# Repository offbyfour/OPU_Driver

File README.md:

# Blu-Ray Lithography
## Introduction
This is the project page for a lithography system based on repurposing Blu-Ray drives. The initial goal is to reach a feature size of at least 500nm (2x the Blu-ray laser spot size). As a stretch goal, we would like to also use the sled and spindle motors as high speed nano-positioners and to spin coat and cure photo-resin.

## Safety
✓ Safety goggles/glasses are absolutely necessary.
A laser dot contains a large amount of energy in such a small space, in the form of light. Your eyes are extremely sensitive to light, and a direct exposure to this very dense energy light for less than a second will blind you for life. We can prevent this by wearing a special type of light filtering glasses, somewhat like the way sunglasses work. But, sunglasses will not work as laser safety glasses. These glasses need to be coated for the correct wavelength. Do not purchase any laser safety glasses under $30, buy from an authorized and reputable seller such as survival lasers. $5 lenses from China will not be sufficient, and have been proven unsafe.

Currently Recommended: https://www.amazon.com/Tool-Klean-Safety-Glasses-Protection/dp/B081BHTJT8/ref=sr_1_5

✓ Be fully aware of what you are pointing at.
With a massive amount of light comes the heat as well. Lasers higher than Class IV (>500mW) burn certain objects very easily, lower powers do burn as well but not as intensely. Lasers like this can most definitely burn furniture such as carpet and couches, hardwood floors, curtains, walls etc. You need to make sure that you are not burning anything against your desire. If the heat build up in an object from a laser is sufficient enough, the object could be set on fire.

✓ Keep in mind of any dangerous objects/surfaces.
Look out for anything noticeably reflective/smooth such as a mirror, polished metal, or even something smooth like a desk. The last thing you want is a laser beam reflected back at you into your eye. Even with safety goggles/glasses, you should not take a chance. Something else dangerous that you need to look out for are flammable items, a high powered laser can easily ignite a match or alcohol. CAREFUL WITH WINDOWS - None are 100% transparent, and WILL reflect a solid beam back towards you, this goes for any type of glass at all. All reflected beams are also a danger and this is no exception. Windows are also a bad thing to be pointing a laser through, you don't know exactly where/what you'll hit.

__________________________________________________

Be careful with lasers, treat them like a loaded gun. It is very easy to create dangerous situations with a laser if you're not careful, be responsible and eliminate that possibility!
Source: laserpointerforums.com
​
## Project Status

Right now, the first project for this technology (Lithography Spinner V1) is in the research/idea stage. See work in progress page for details on upcoming tasks if you want to contribute.

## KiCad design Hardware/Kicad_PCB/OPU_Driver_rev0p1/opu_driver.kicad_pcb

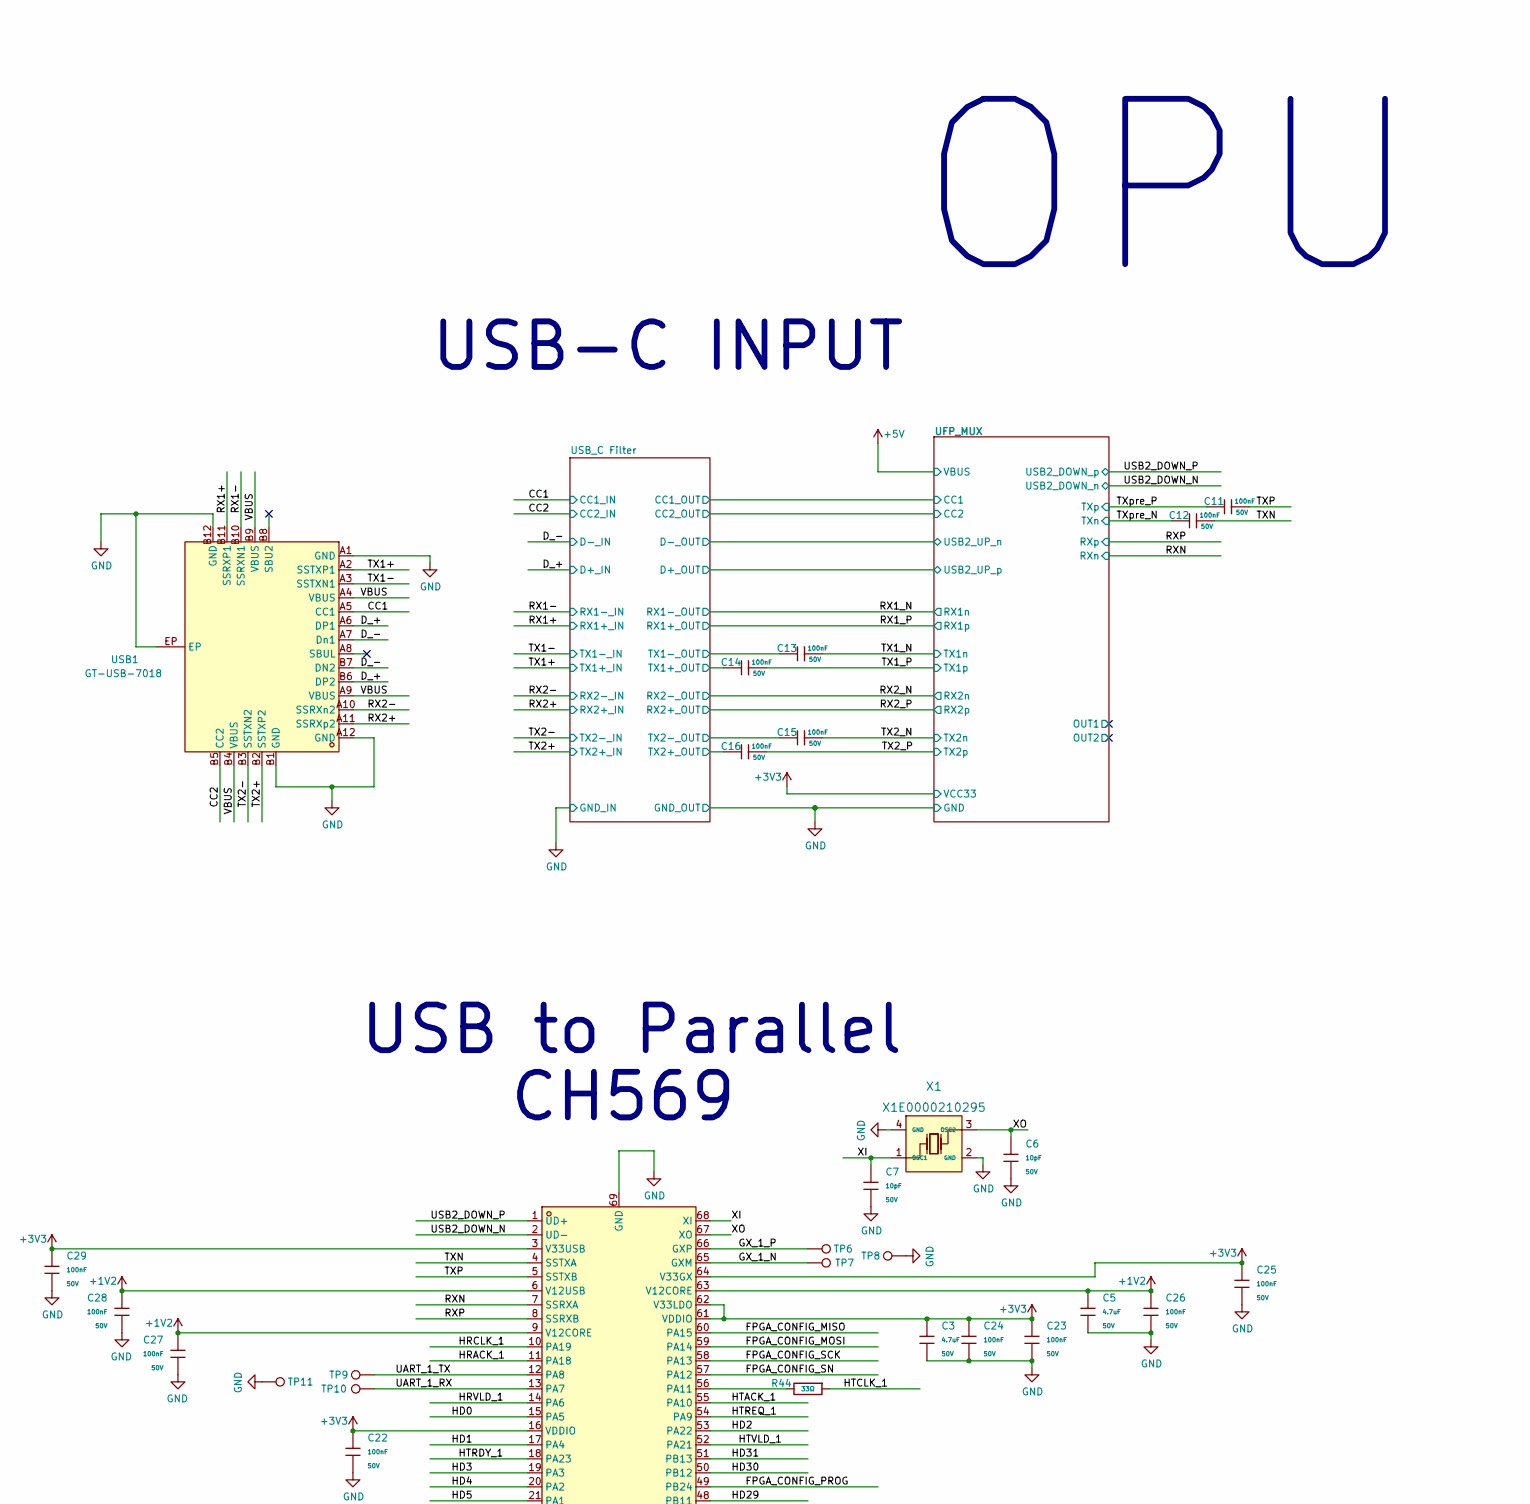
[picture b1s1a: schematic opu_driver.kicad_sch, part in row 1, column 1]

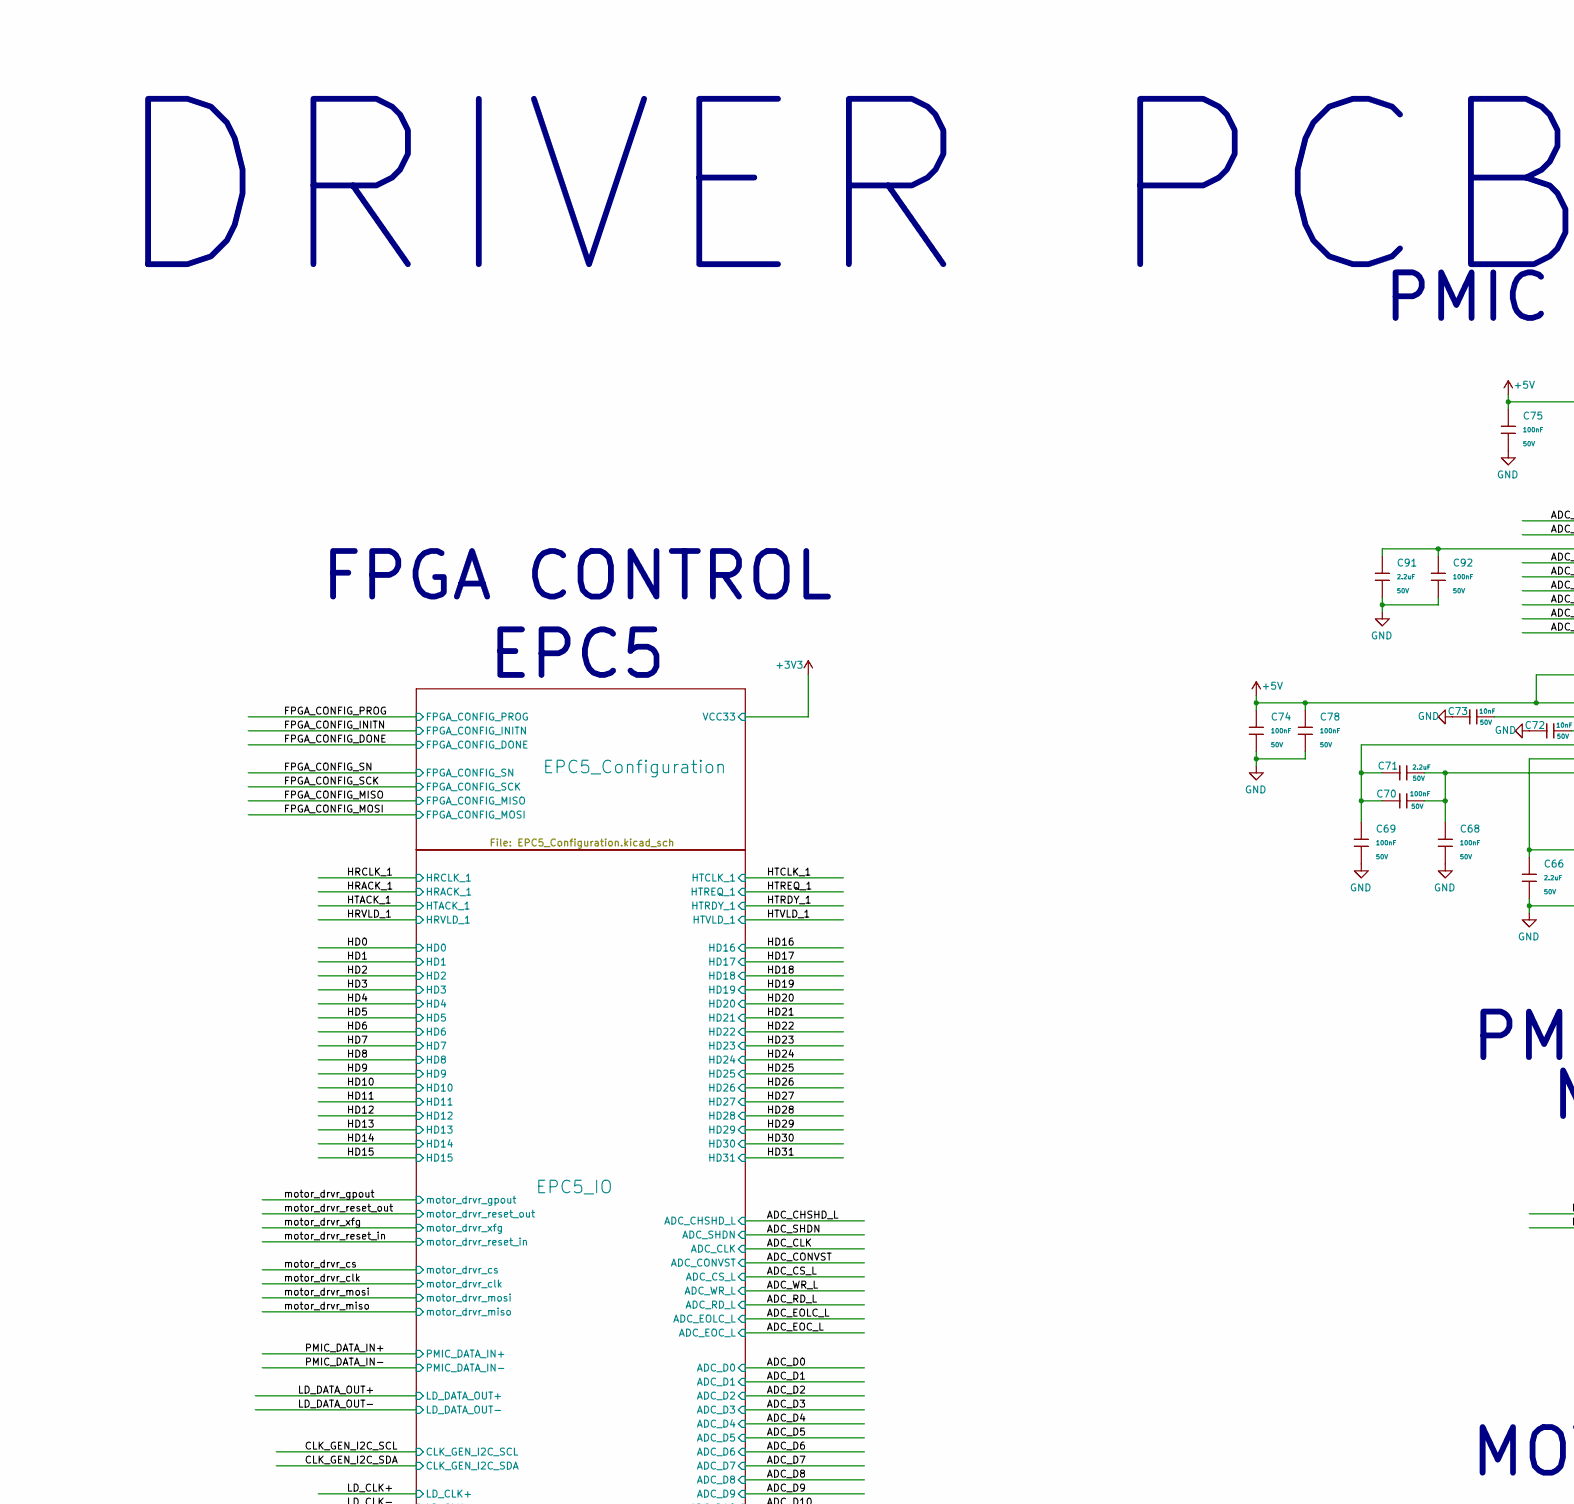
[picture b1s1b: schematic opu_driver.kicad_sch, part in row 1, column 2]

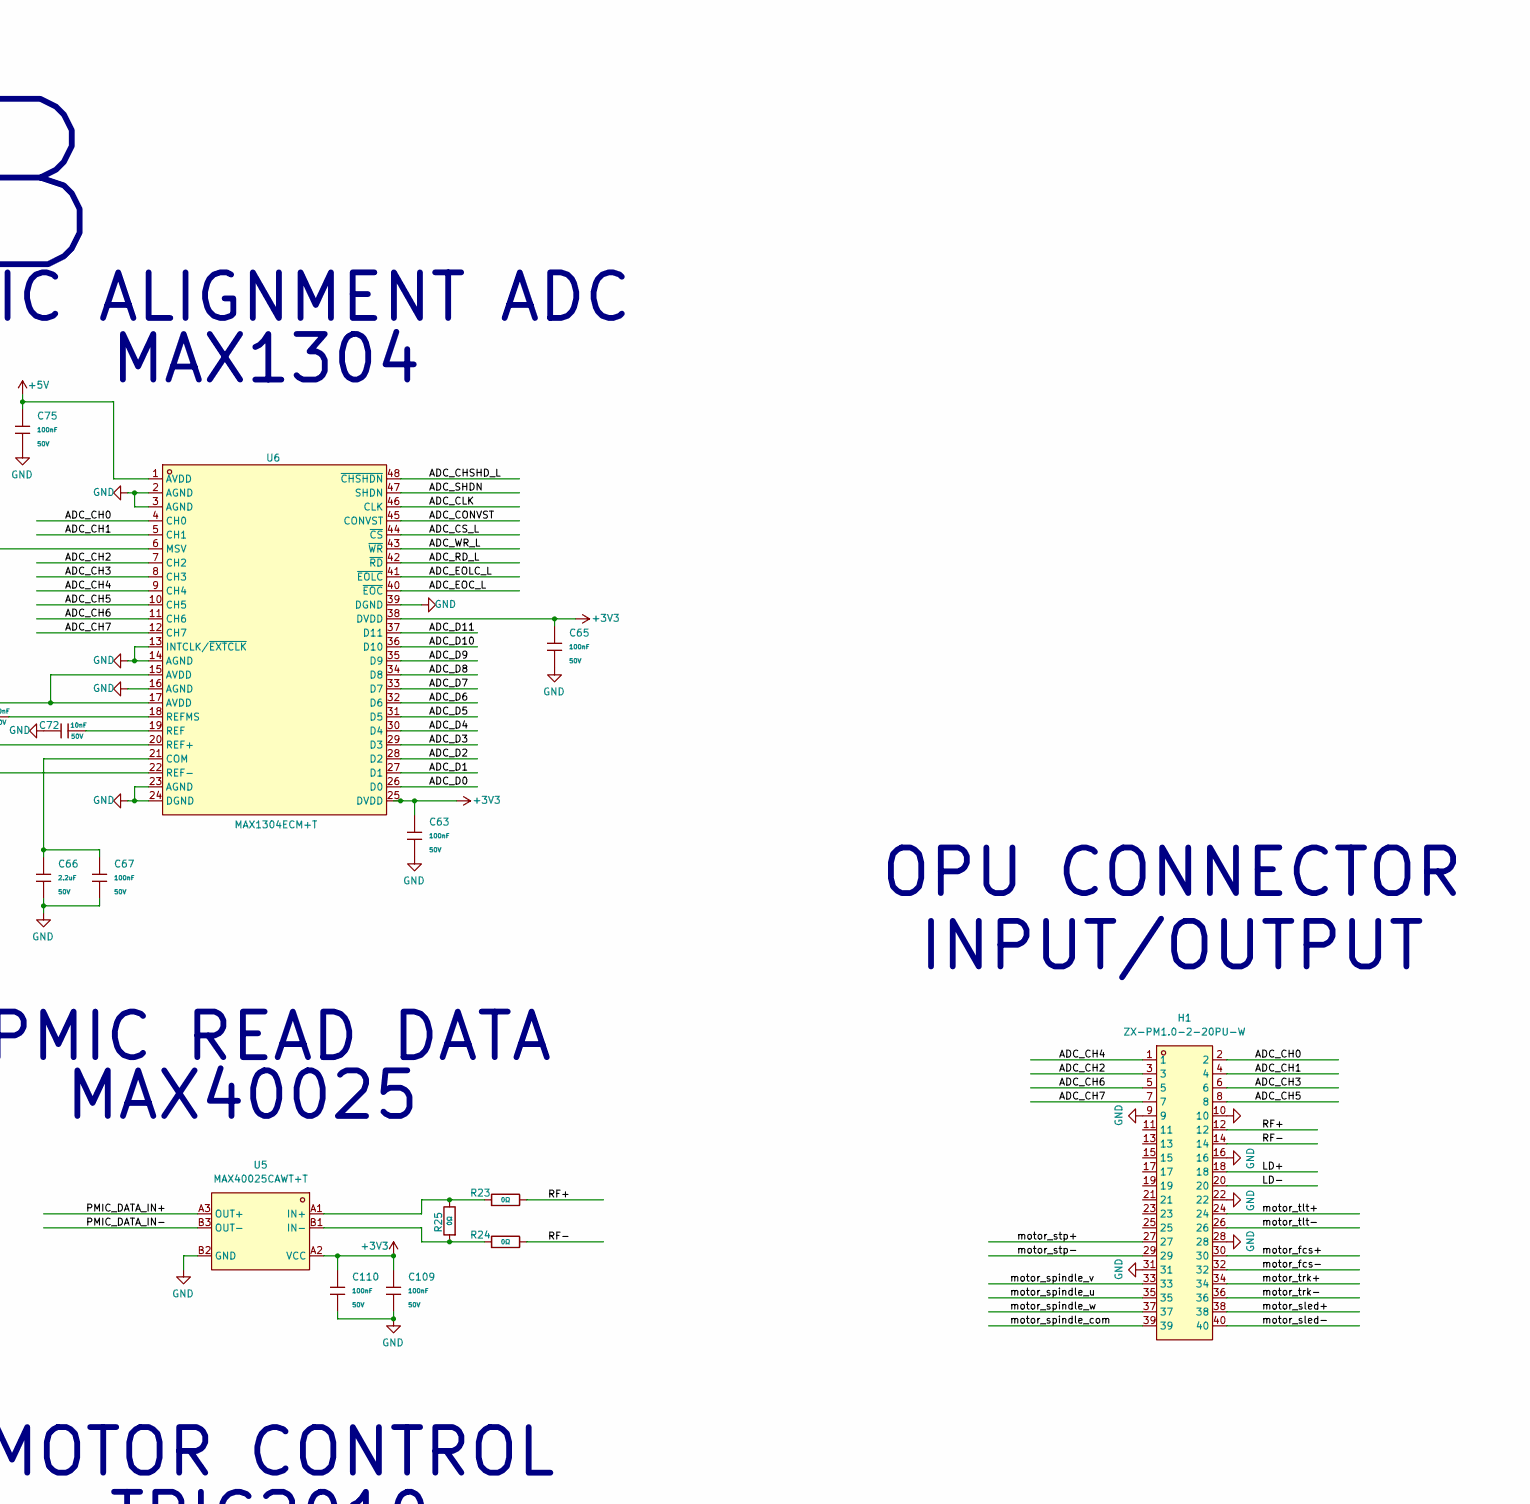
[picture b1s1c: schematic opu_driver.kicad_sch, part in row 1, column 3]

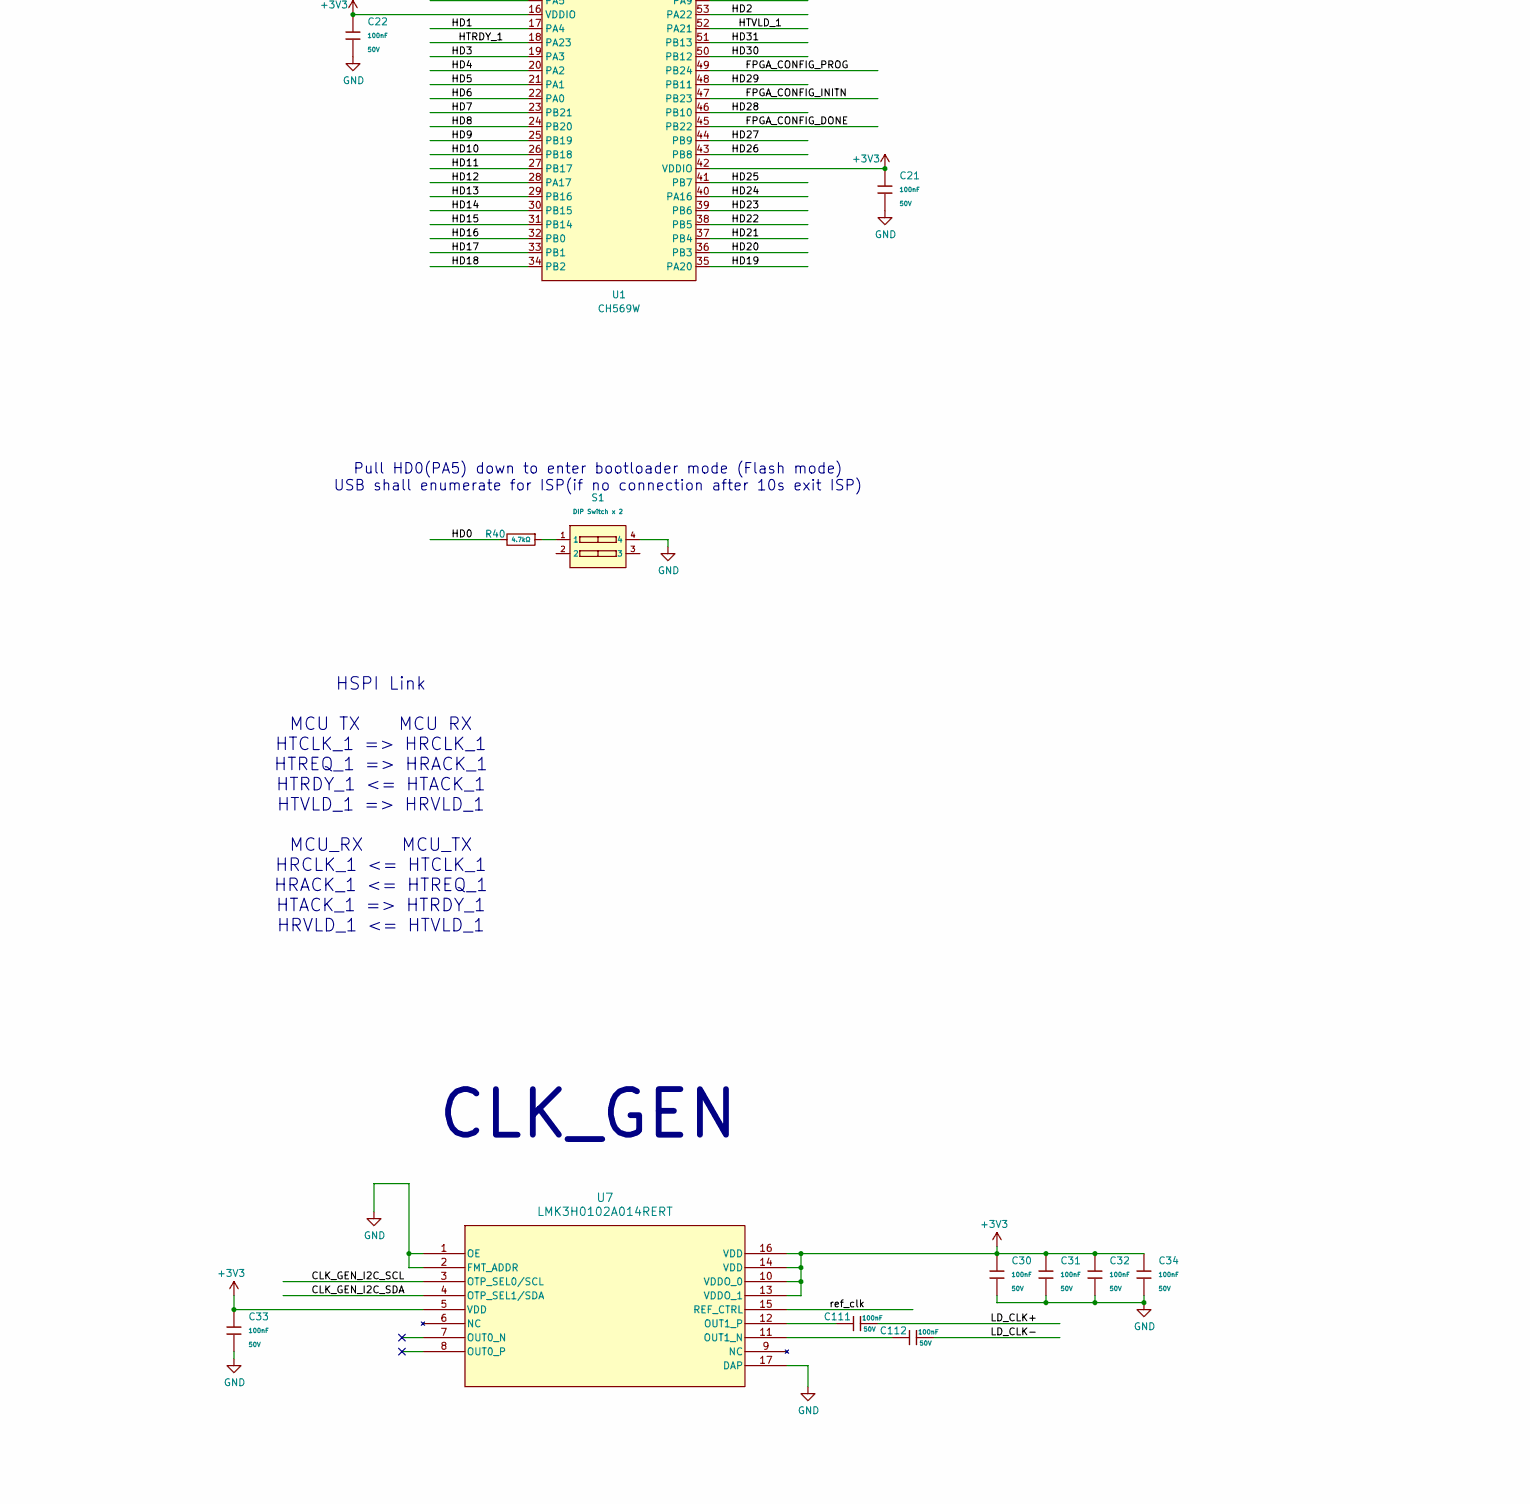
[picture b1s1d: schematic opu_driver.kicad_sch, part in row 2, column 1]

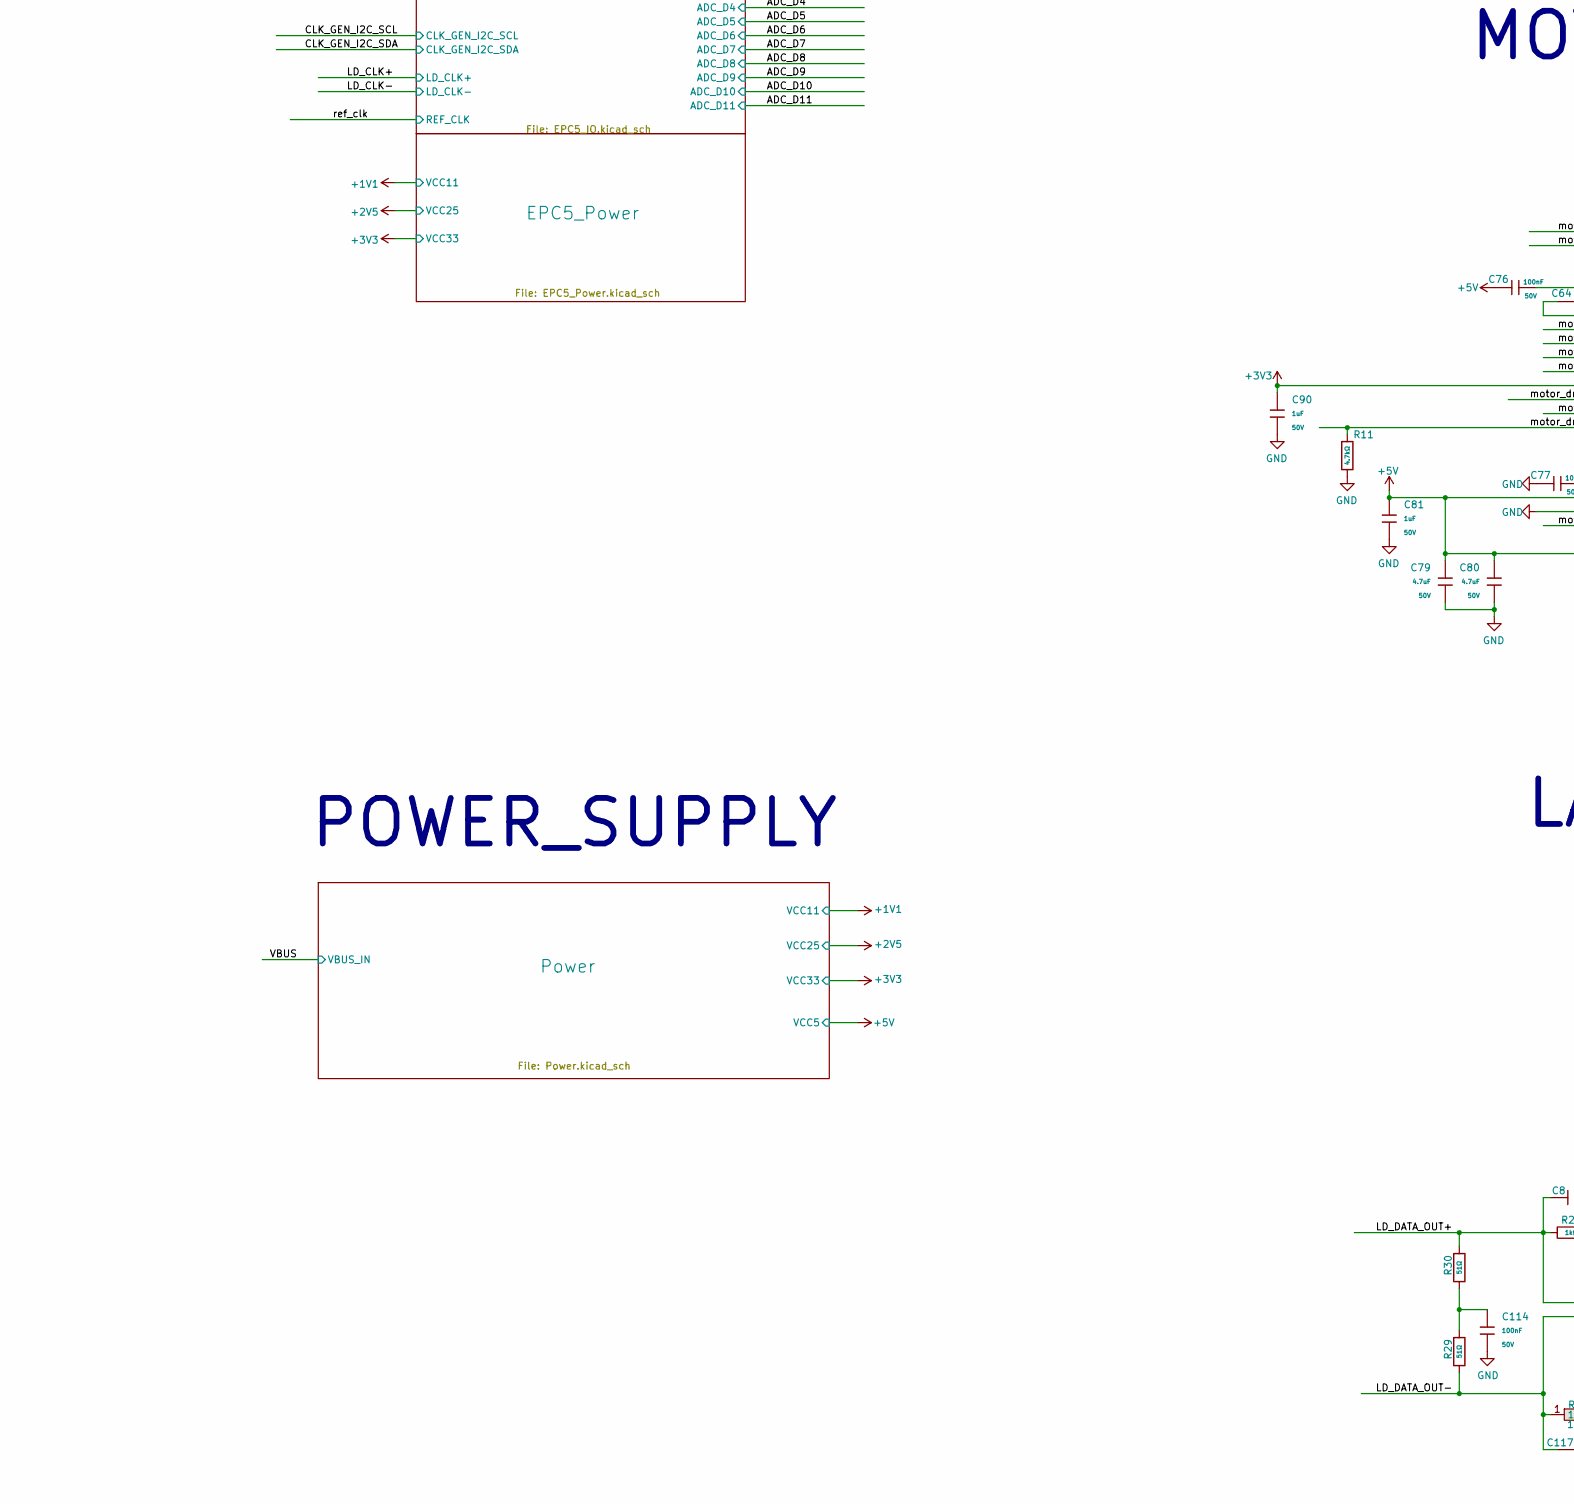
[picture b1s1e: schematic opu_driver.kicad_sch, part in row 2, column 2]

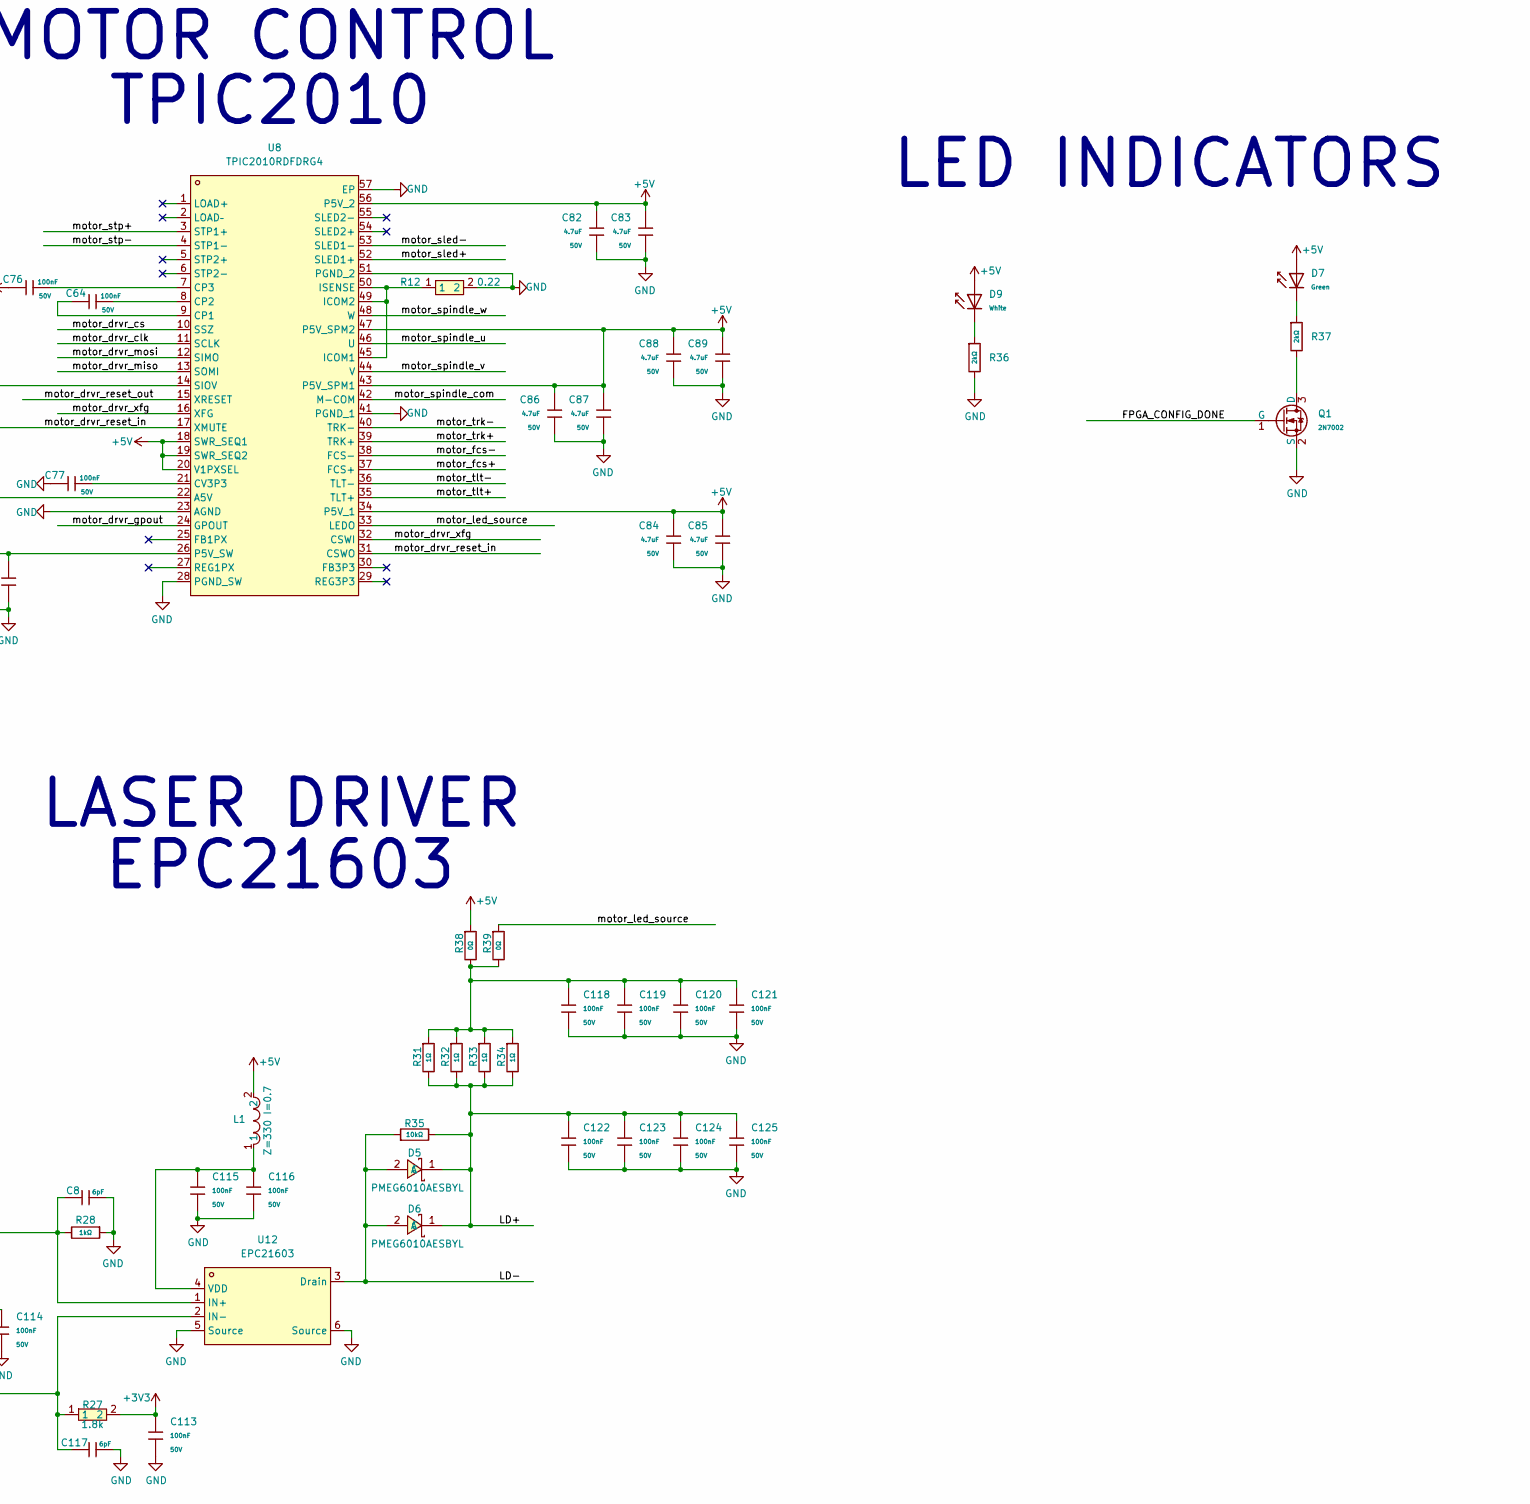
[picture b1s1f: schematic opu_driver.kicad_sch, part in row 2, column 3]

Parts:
C3, C5, C79, C80, C82, C83, C84, C85, C86, C87, C88, C89: 4.7uF; C_1206; Voltage Rated 50V; Tolerance ±10%; Part 1206B475K500NT; LCSC C29823
C6, C7: 10pF; C_0402; Voltage Rated 50V; Tolerance ±5%; Part CL05C100JB5NNNC; LCSC C32949
C8, C117: 6pF; C_0402; Part 0402CG6R0C500NT (SMT业务专用); LCSC C30274
C11, C12, C13, C14, C15, C16, C21, C22, C23, C24, C25, C26, C27, C28, C29, C30, C31, C32, C33, C34, C63, C64, C65, C67, C68, C69, C70, C74, C75, C76, C77, C78, C92, C109, C110, C111, C112, C113, C114, C115, C116, C118, C119, C120, C121, C122, C123, C124, C125: 100nF; C_0402; Voltage Rated 50V; Tolerance ±10%; Part CL05B104KB54PNC; LCSC C307331
C66, C71, C91: 2.2uF; C_1206; Voltage Rated 50V; Tolerance ±10%; Part CL31B225KBHNNNE; LCSC C50254
C72, C73: 10nF; C_0402; Voltage Rated 50V; Tolerance ±10%; Part CL05B103KB5NNNC; LCSC C15195
C81, C90: 1uF; C_0805; Voltage Rated 50V; Tolerance ±10%; Part CL21B105KBFNNNE; LCSC C28323
D5, D6: PMEG6010AESBYL; X1SON-2_L1.0-W0.6-P0.65-RD; LCSC Part C552929
D7: Green; D_0603; Part 19-217/GHC-YR1S2/6T; LCSC C2986059
D9: White; D_0603; Part KT-0603W; LCSC C2290
H1: ZX-PM1.0-2-20PU-W; HDR-SMD_40P-P1.00-V-F-R2-C20-LS3.8; LCSC Part C41369836
L1: BLM15EX331SN1D; L0402; LCSC Part C596498
Q1: 2N7002; Q_SOT-23; Part 2N7002; LCSC C8545
R11, R40: 4.7kΩ; R_0402; Overload Voltage (Max) 50V; Tolerance ±1%; Part 0402WGF4701TCE; LCSC C25900
R12: CR2512J1R220G; R2512; LCSC Part C5381546
R23, R24, R25: 0Ω; R_0402; Overload Voltage (Max) 50V; Tolerance ±1%; Part 0402WGF0000TCE; LCSC C17168
R27: RC0402FR-071K8L; R0402; LCSC Part C163481
R28: 1kΩ; R_0402; Overload Voltage (Max) 50V; Tolerance ±1%; Part 0402WGF1001TCE; LCSC C11702
R29, R30: 51Ω; R_0402; Overload Voltage (Max) 50V; Tolerance ±1%; Part 0402WGF510JTCE; LCSC C25125
R31, R32, R33, R34: 1Ω; R_0805; Overload Voltage (Max) 150V; Tolerance ±1%; Part 0805W8F100KT5E; LCSC C25271
R35: 10kΩ; R_0402; Overload Voltage (Max) 50V; Tolerance ±1%; Part 0402WGF1002TCE; LCSC C25744
R36, R37: 2kΩ; R_0402; Overload Voltage (Max) 50V; Tolerance ±1%; Part 0402WGF2001TCE; LCSC C4109
R38, R39: 0Ω; R_0603; Overload Voltage (Max) 75V; Tolerance ±1%; Part 0603WAF0000T5E; LCSC C21189
R44: 33Ω; R_0402; Overload Voltage (Max) 50V; Tolerance ±1%; Part 0402WGF330JTCE; LCSC C25105
S1: DIP Switch x 2; SW-SMD_218-2LPSTRF; Current Rating 25mA; Voltage Rating 24V; Part 218-2LPSTR; LCSC C2961921
TP6, TP7, TP8, TP9, TP10, TP11: TestPoint; TestPoint_Pad_D1.0mm
U1: CH569W; QFN-68_L8.0-W8.0-P0.40-BL-EP5.5; LCSC Part C2857462
U5: MAX40025CAWT+T; WLP-6_L1.2-W0.8-R2-C3-P0.40-TL_MAX40111ANT; LCSC Part C7451830
U6: MAX1304ECM+T; TQFP-48_L7.0-W7.0-P0.50-LS9.0-BL; LCSC Part C2670670
U7: LMK3H0102A014RERT; TQFN16_RER_TEX
U8: TPIC2010RDFDRG4; HTSSOP-56_L14.0-W6.0-P0.50-LS8.1-BL-EP; LCSC Part C702134
U12: EPC21603; BGA-6_L1.5-W1.0-P0.50-TL; LCSC Part C6191277
USB1: GT-USB-7018; TYPE-C-SMD_GT-USB-7018; LCSC Part C2762978
X1: X1E0000210295; CRYSTAL-SMD_4P-L3.2-W2.5-BL; LCSC Part C255930

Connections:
+1V2: C5.1, C26.1, C27.1, C28.1, U1.6 (V12USB), U1.9 (V12CORE), U1.63 (V12CORE)
+3V3: C3.1, C21.1, C22.1, C23.1, C24.1, C25.1, C29.1, C30.1, C31.1, C32.1, C33.1, C34.1, C63.1, C65.1, C90.1, C109.1, C110.1, C113.1, R27.2, U1.3 (V33USB), U1.16 (VDDIO), U1.42 (VDDIO), U1.61 (VDDIO), U1.62 (V33LDO), U1.64 (V33GX), U5.A2 (VCC), U6.25 (DVDD), U6.38 (DVDD), U7.5 (VDD), U7.10 (VDDO_0), U7.13 (VDDO_1), U7.14 (VDD), U7.16 (VDD), U8.14 (SIOV); also elsewhere on the board
/ADC_CH0: H1.2, U6.4 (CH0)
/ADC_CH1: H1.4, U6.5 (CH1)
/ADC_CH2: H1.3, U6.7 (CH2)
/ADC_CH3: H1.6, U6.8 (CH3)
/ADC_CH4: H1.1, U6.9 (CH4)
/ADC_CH5: H1.8, U6.10 (CH5)
/ADC_CH6: H1.5, U6.11 (CH6)
/ADC_CH7: H1.7, U6.12 (CH7)
/ADC_CHSHD_L: U6.48 (~CHSHDN); also elsewhere on the board
/ADC_CLK: U6.46 (CLK); also elsewhere on the board
/ADC_CONVST: U6.45 (CONVST); also elsewhere on the board
/ADC_CS_L: U6.44 (~CS); also elsewhere on the board
/ADC_D0: U6.26 (D0); also elsewhere on the board
/ADC_D1: U6.27 (D1); also elsewhere on the board
/ADC_D2: U6.28 (D2); also elsewhere on the board
/ADC_D3: U6.29 (D3); also elsewhere on the board
/ADC_D4: U6.30 (D4); also elsewhere on the board
/ADC_D5: U6.31 (D5); also elsewhere on the board
/ADC_D6: U6.32 (D6); also elsewhere on the board
/ADC_D7: U6.33 (D7); also elsewhere on the board
/ADC_D8: U6.34 (D8); also elsewhere on the board
/ADC_D9: U6.35 (D9); also elsewhere on the board
/ADC_D10: U6.36 (D10); also elsewhere on the board
/ADC_D11: U6.37 (D11); also elsewhere on the board
/ADC_EOC_L: U6.40 (~EOC); also elsewhere on the board
/ADC_EOLC_L: U6.41 (~EOLC); also elsewhere on the board
/ADC_RD_L: U6.42 (~RD); also elsewhere on the board
/ADC_SHDN: U6.47 (SHDN); also elsewhere on the board
/ADC_WR_L: U6.43 (~WR); also elsewhere on the board
/CC1: USB1.A5 (CC1); also elsewhere on the board
/CC2: USB1.B5 (CC2); also elsewhere on the board
/CLK_GEN_I2C_SCL: U7.3 (OTP_SEL0/SCL); also elsewhere on the board
/CLK_GEN_I2C_SDA: U7.4 (OTP_SEL1/SDA); also elsewhere on the board
/D_+: U1.1 (UD+), USB1.A6 (DP1), USB1.B6 (DP2); also elsewhere on the board
/D_-: U1.2 (UD-), USB1.A7 (Dn1), USB1.B7 (DN2); also elsewhere on the board
/FPGA_CONFIG_DONE: Q1.1 (G), U1.45 (PB22); also elsewhere on the board
/FPGA_CONFIG_INITN: U1.47 (PB23); also elsewhere on the board
/FPGA_CONFIG_MISO: U1.60 (PA15); also elsewhere on the board
/FPGA_CONFIG_MOSI: U1.59 (PA14); also elsewhere on the board
/FPGA_CONFIG_PROG: U1.49 (PB24); also elsewhere on the board
/FPGA_CONFIG_SCK: U1.58 (PA13); also elsewhere on the board
/FPGA_CONFIG_SN: U1.57 (PA12); also elsewhere on the board
/GX_1_N: TP7.1, U1.65 (GXM)
/GX_1_P: TP6.1, U1.66 (GXP)
/HD0: R40.2, U1.15 (PA5); also elsewhere on the board
/HD1: U1.17 (PA4); also elsewhere on the board
/HD2: U1.53 (PA22); also elsewhere on the board
/HD3: U1.19 (PA3); also elsewhere on the board
/HD4: U1.20 (PA2); also elsewhere on the board
/HD5: U1.21 (PA1); also elsewhere on the board
/HD6: U1.22 (PA0); also elsewhere on the board
/HD7: U1.23 (PB21); also elsewhere on the board
/HD8: U1.24 (PB20); also elsewhere on the board
/HD9: U1.25 (PB19); also elsewhere on the board
/HD10: U1.26 (PB18); also elsewhere on the board
/HD11: U1.27 (PB17); also elsewhere on the board
/HD12: U1.28 (PA17); also elsewhere on the board
/HD13: U1.29 (PB16); also elsewhere on the board
/HD14: U1.30 (PB15); also elsewhere on the board
/HD15: U1.31 (PB14); also elsewhere on the board
/HD16: U1.32 (PB0); also elsewhere on the board
/HD17: U1.33 (PB1); also elsewhere on the board
/HD18: U1.34 (PB2); also elsewhere on the board
/HD19: U1.35 (PA20); also elsewhere on the board
/HD20: U1.36 (PB3); also elsewhere on the board
/HD21: U1.37 (PB4); also elsewhere on the board
/HD22: U1.38 (PB5); also elsewhere on the board
/HD23: U1.39 (PB6); also elsewhere on the board
/HD24: U1.40 (PA16); also elsewhere on the board
/HD25: U1.41 (PB7); also elsewhere on the board
/HD26: U1.43 (PB8); also elsewhere on the board
/HD27: U1.44 (PB9); also elsewhere on the board
/HD28: U1.46 (PB10); also elsewhere on the board
/HD29: U1.48 (PB11); also elsewhere on the board
/HD30: U1.50 (PB12); also elsewhere on the board
/HD31: U1.51 (PB13); also elsewhere on the board
/HRACK_1: U1.11 (PA18); also elsewhere on the board
/HRCLK_1: U1.10 (PA19); also elsewhere on the board
/HRVLD_1: U1.14 (PA6); also elsewhere on the board
/HTACK_1: U1.55 (PA10); also elsewhere on the board
/HTCLK_1: R44.1; also elsewhere on the board
/HTRDY_1: U1.18 (PA23); also elsewhere on the board
/HTREQ_1: U1.54 (PA9); also elsewhere on the board
/HTVLD_1: U1.52 (PA21); also elsewhere on the board
/LD+: C122.1, C123.1, C124.1, C125.1, D5.1 (C), D6.1 (C), H1.18, R31.2, R32.2, R33.2, R34.2, R35.2
/LD-: D5.2 (A), D6.2 (A), H1.20, R35.1, U12.3 (Drain)
/LD_CLK+: C111.2; also elsewhere on the board
/LD_CLK-: C112.2; also elsewhere on the board
/LD_DATA_OUT+: C8.1, R28.2, R30.1, U12.1 (IN+); also elsewhere on the board
/LD_DATA_OUT-: C117.1, R27.1, R29.2, U12.2 (IN-); also elsewhere on the board
/PMIC_DATA_IN+: U5.A3 (OUT+); also elsewhere on the board
/PMIC_DATA_IN-: U5.B3 (OUT-); also elsewhere on the board
/RF+: H1.12, R23.2
/RF-: H1.14, R24.2
/RX1+: USB1.B11 (SSRXP1); also elsewhere on the board
/RX1-: USB1.B10 (SSRXN1); also elsewhere on the board
/RX2+: USB1.A11 (SSRXp2); also elsewhere on the board
/RX2-: USB1.A10 (SSRXn2); also elsewhere on the board
/RXN: U1.7 (SSRXA); also elsewhere on the board
/RXP: U1.8 (SSRXB); also elsewhere on the board
/TX1+: C14.2, USB1.A2 (SSTXP1); also elsewhere on the board
/TX1-: C13.2, USB1.A3 (SSTXN1); also elsewhere on the board
/TX1_N: C13.1; also elsewhere on the board
/TX1_P: C14.1; also elsewhere on the board
/TX2+: C16.2, USB1.B2 (SSTXP2); also elsewhere on the board
/TX2-: C15.2, USB1.B3 (SSTXN2); also elsewhere on the board
/TX2_N: C15.1; also elsewhere on the board
/TX2_P: C16.1; also elsewhere on the board
/TXN: C12.1, U1.4 (SSTXA)
/TXP: C11.1, U1.5 (SSTXB)
/TXpre_N: C12.2; also elsewhere on the board
/TXpre_P: C11.2; also elsewhere on the board
/UART_1_RX: TP10.1, U1.13 (PA7)
/UART_1_TX: TP9.1, U1.12 (PA8)
/VBUS: USB1.A4 (VBUS), USB1.A9 (VBUS), USB1.B4 (VBUS), USB1.B9 (VBUS); also elsewhere on the board
/XO: C6.1, U1.67 (XO), X1.3 (OSC2)
/motor_drvr_clk: U8.11 (SCLK); also elsewhere on the board
/motor_drvr_cs: U8.10 (SSZ); also elsewhere on the board
/motor_drvr_gpout: U8.24 (GPOUT); also elsewhere on the board
/motor_drvr_miso: U8.13 (SOMI); also elsewhere on the board
/motor_drvr_mosi: U8.12 (SIMO); also elsewhere on the board
/motor_drvr_reset_in: R11.1, U8.17 (XMUTE), U8.31 (CSWO); also elsewhere on the board
/motor_drvr_reset_out: U8.15 (XRESET); also elsewhere on the board
/motor_drvr_xfg: U8.16 (XFG), U8.32 (CSWI); also elsewhere on the board
/motor_fcs+: H1.30, U8.37 (FCS+)
/motor_fcs-: H1.32, U8.38 (FCS-)
/motor_led_source: R39.1, U8.33 (LEDO)
/motor_sled+: H1.38, U8.52 (SLED1+)
/motor_sled-: H1.40, U8.53 (SLED1-)
/motor_spindle_com: H1.39, U8.42 (M-COM)
/motor_spindle_u: H1.35, U8.46 (U)
/motor_spindle_v: H1.33, U8.44 (V)
/motor_spindle_w: H1.37, U8.48 (W)
/motor_stp+: H1.27, U8.3 (STP1+)
/motor_stp-: H1.29, U8.4 (STP1-)
/motor_tlt+: H1.24, U8.35 (TLT+)
/motor_tlt-: H1.26, U8.36 (TLT-)
/motor_trk+: H1.34, U8.39 (TRK+)
/motor_trk-: H1.36, U8.40 (TRK-)
/ref_clk: U7.15 (REF_CTRL); also elsewhere on the board
GND: C3.2, C5.2, C6.2, C7.2, C8.2, C21.2, C22.2, C23.2, C24.2, C25.2, C26.2, C27.2, C28.2, C29.2, C30.2, C31.2, C32.2, C33.2, C34.2, C63.2, C65.2, C66.2, C67.2, C68.2, C69.2, C72.2, C73.2, C74.2, C75.2, C77.2, C78.2, C79.2, C80.2, C81.2, C82.2, C83.2, C84.2, C85.2, C86.2, C87.2, C88.2, C89.2, C90.2, C91.2, C92.2, C109.2, C110.2, C113.2, C114.2, C115.2, C116.2, C117.2, C118.2, C119.2, C120.2, C121.2, C122.2, C123.2, C124.2, C125.2, H1.9, H1.10, H1.16, H1.22, H1.28, H1.31, Q1.2 (S), R11.2, R12.2, R28.1, R36.2, S1.4, TP8.1, TP11.1, U1.69 (GND), U5.B2 (GND), U6.2 (AGND), U6.3 (AGND), U6.13 (INTCLK/~EXTCLK), U6.14 (AGND), U6.16 (AGND), U6.23 (AGND), U6.24 (DGND), U6.39 (DGND), U7.1 (OE), U7.2 (FMT_ADDR), U7.17 (DAP), U8.23 (AGND), U8.28 (PGND_SW), U8.41 (PGND_1), U8.51 (PGND_2), U8.57 (EP), U12.5 (Source), U12.6 (Source), USB1.A1 (GND), USB1.A12 (GND), USB1.B1 (GND), USB1.B12 (GND), USB1.EP, X1.2 (GND), X1.4 (GND); also elsewhere on the board
unnamed: C114.1, R29.1, R30.2
unnamed: C118.1, C119.1, C120.1, C121.1, R31.1, R32.1, R33.1, R34.1, R38.2, R39.2
unnamed: D7.1, R37.1
unnamed: D9.1, R36.1
unnamed: Q1.3 (D), R37.2
unnamed: R40.1, S1.1
unnamed: R44.2, U1.56 (PA11)
unnamed: R23.1, R25.2, U5.A1 (IN+)
unnamed: R24.1, R25.1, U5.B1 (IN-)
unnamed: C66.1, C67.1, U6.21 (COM)
unnamed: C91.1, C92.1, U6.6 (MSV)
unnamed: C72.1, U6.19 (REF)
unnamed: C69.1, C70.1, C71.1, U6.20 (REF+)
unnamed: C68.1, C70.2, C71.2, U6.22 (REF-)
unnamed: C73.1, U6.18 (REFMS)
unnamed: C112.1, U7.11 (OUT1_N)
unnamed: C111.1, U7.12 (OUT1_P)
unnamed: C64.2, U8.9 (CP1)
unnamed: C64.1, U8.8 (CP2)
unnamed: C76.1, U8.7 (CP3)
unnamed: C77.1, U8.21 (CV3P3)
unnamed: R12.1, U8.45 (ICOM1), U8.49 (ICOM2), U8.50 (ISENSE)
unnamed: C115.1, C116.1, L1.1, U12.4 (VDD)

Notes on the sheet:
MOTOR CONTROL
LASER DRIVER
USB-C INPUT
TPIC2010
EPC21603
OPU DRIVER PCB
PMIC READ DATA
EPC5
MAX1304
CH569
HSPI Link MCU TX MCU RX HTCLK_1 => HRCLK_1 HTREQ_1 => HRACK_1 HTRDY_1 <= HTACK_1 HTVLD_1 => HRVLD_1 MCU_RX MCU_TX HRCLK_1 <= HTCLK_1 HRACK_1 <= HTREQ_1 HTACK_1 => HTRDY_1 HRVLD_1 <= HTVLD_1
CLK_GEN
USB to Parallel
LED INDICATORS
OPU CONNECTOR INPUT/OUTPUT
PMIC ALIGNMENT ADC
FPGA CONTROL
POWER_SUPPLY
MAX40025
Pull HD0(PA5) down to enter bootloader mode (Flash mode) USB shall enumerate for ISP(if no connection after 10s exit ISP)

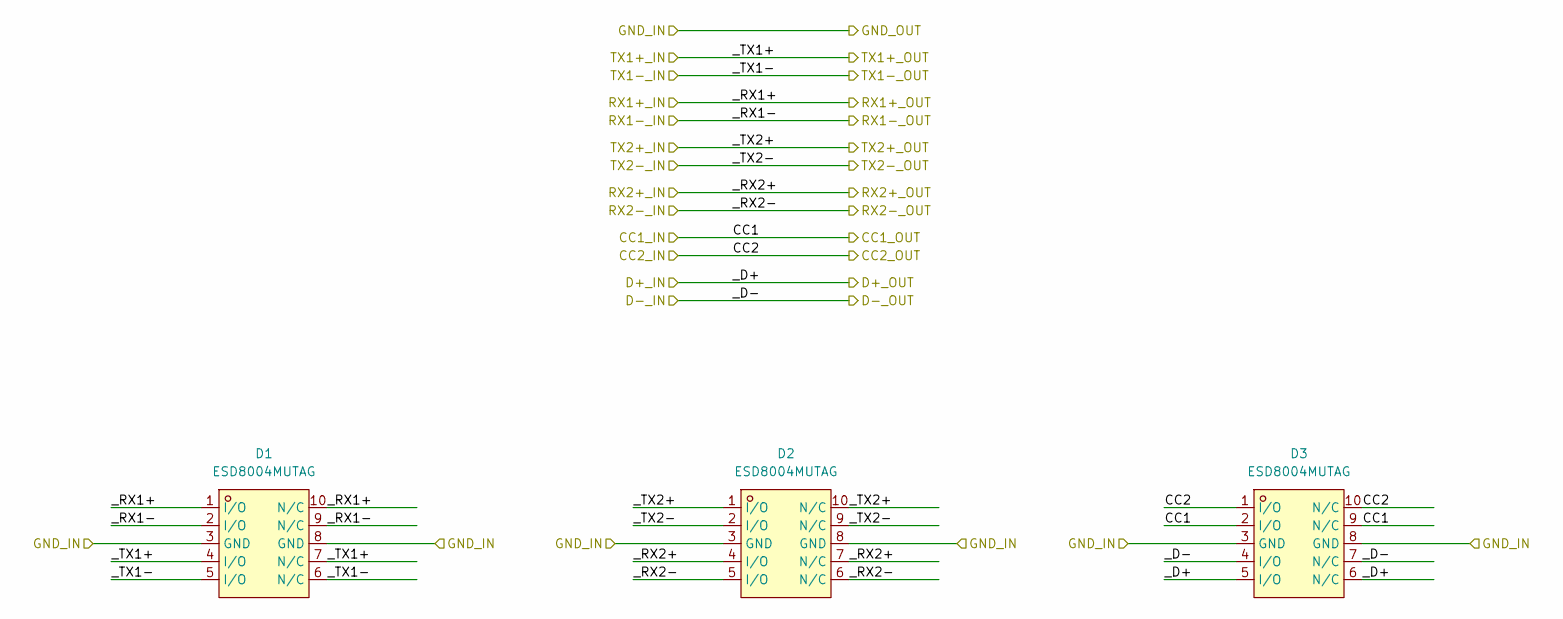
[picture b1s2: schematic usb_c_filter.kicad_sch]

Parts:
D1, D2, D3: ESD8004MUTAG; UDFN-10_L2.5-W1.0-P0.50-BL; LCSC Part C605399

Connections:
/CC1: D3.2 (I/O), D3.9 (N/C); also elsewhere on the board
/CC2: D3.1 (I/O), D3.10 (N/C); also elsewhere on the board
/D_+: D3.5 (I/O), D3.6 (N/C); also elsewhere on the board
/D_-: D3.4 (I/O), D3.7 (N/C); also elsewhere on the board
/RX1+: D1.1 (I/O), D1.10 (N/C); also elsewhere on the board
/RX1-: D1.2 (I/O), D1.9 (N/C); also elsewhere on the board
/RX2+: D2.4 (I/O), D2.7 (N/C); also elsewhere on the board
/RX2-: D2.5 (I/O), D2.6 (N/C); also elsewhere on the board
/TX1+: D1.4 (I/O), D1.7 (N/C); also elsewhere on the board
/TX1-: D1.5 (I/O), D1.6 (N/C); also elsewhere on the board
/TX2+: D2.1 (I/O), D2.10 (N/C); also elsewhere on the board
/TX2-: D2.2 (I/O), D2.9 (N/C); also elsewhere on the board
GND: D1.3 (GND), D1.8 (GND), D2.3 (GND), D2.8 (GND), D3.3 (GND), D3.8 (GND); also elsewhere on the board
